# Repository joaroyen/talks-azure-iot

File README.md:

# NNUG Trondheim: .NET and Azure IoT

This repository contains my presentation from NNUG Trondheim on January 30, 2020. 

The presentation is in Norwegian and is hosted on GitHub pages: [https://joaroyen.github.io/talks-azure-iot](https://joaroyen.github.io/talks-azure-iot).

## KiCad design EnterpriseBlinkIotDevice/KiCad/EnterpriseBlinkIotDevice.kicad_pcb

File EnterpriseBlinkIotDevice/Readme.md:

# Rev 1

Denne utgaven fungerte ikke da TIP 120 kan kun switcje opp til base spenning. Løsning var å enre til å switche til GND ved å bodge en av skruterminalene til GND og bytte om hvor Load kobles til. 

# Rev 2

- TIP120 switcher GND og ikke 12V
- Så kort som mulig avstand til "høy spenning"
- Pull-down til IO pin for å forhindre at transistoren skrur på LED når ESP8266 får strøm / bootes
- Marker positiv skruterminal med spenning
- Korrekt footprint for motstandene
- Monteringshull

# Rev 3

- Byttet om 12V og Load terminaler
- Flyttet R1 og R2 litt lengre ned

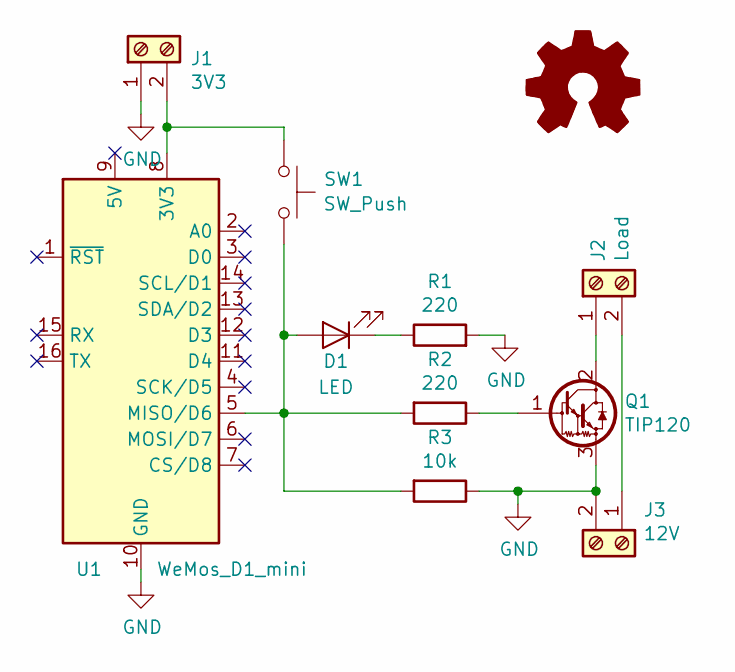
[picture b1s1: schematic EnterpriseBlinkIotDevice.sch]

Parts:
D1: LED; LED_D3.0mm
J1: 3V3; TerminalBlock_bornier-2_P5.08mm
J2: Load; TerminalBlock_bornier-2_P5.08mm
J3: 12V; TerminalBlock_bornier-2_P5.08mm
Q1: TIP120; TO-220-3_Vertical
R1, R2: 220; R_Axial_DIN0207_L6.3mm_D2.5mm_P10.16mm_Horizontal
R3: 10k; R_Axial_DIN0207_L6.3mm_D2.5mm_P10.16mm_Horizontal
SW1: SW_Push; SW_PUSH_6mm
U1: WeMos_D1_mini; WEMOS_D1_mini_light

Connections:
GND: J1.1, J3.2, Q1.3 (E), R1.2, R3.1, U1.10 (GND)
unnamed: D1.1 (K), R1.1
unnamed: D1.2 (A), R2.2, R3.2, SW1.2, U1.5 (MISO/D6)
unnamed: J1.2, SW1.1, U1.8 (3V3)
unnamed: J2.1, Q1.2 (C)
unnamed: J2.2, J3.1
unnamed: Q1.1 (B), R2.1

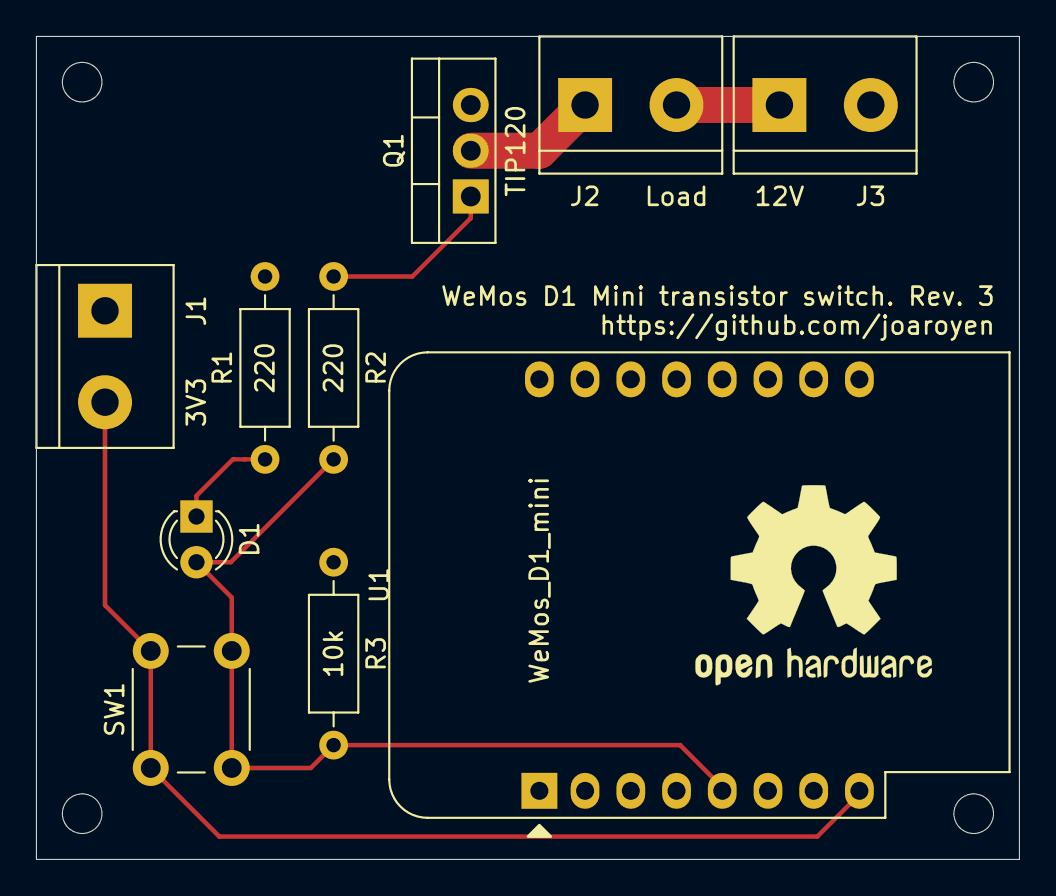
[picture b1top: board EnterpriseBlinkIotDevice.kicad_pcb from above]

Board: 2 copper layers, 54.6 x 45.7 mm, 10 parts (0 on the bottom side), 7 nets.

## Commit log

2020-01-30 Release 1
2020-01-30 Added link to GitHub pages
2022-06-22 Bump Newtonsoft.Json in /EchoFunctionApp/GoogleSmartHome
    Bumps [Newtonsoft.Json](https://github.com/JamesNK/Newtonsoft.Json) from 12.0.3 to 13.0.1.
    - [Release notes](https://github.com/JamesNK/Newtonsoft.Json/releases)
    - [Commits](https://github.com/JamesNK/Newtonsoft.Json/compare/12.0.3...13.0.1)
    ---
    updated-dependencies:
    - dependency-name: Newtonsoft.Json
